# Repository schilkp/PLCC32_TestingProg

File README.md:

# PLCC_TestingProg
### Philipp Schilk

A board for programming/testing the SST39SF040 flash IC. 
It includes a PLCC32 Socket, breakouts of the Data, Address and Control Lines,
and optional shift registers to drive the address lines during programming.

Furthermore, if nothing but the PLCC32 socket is fitted, it may serve as a direct
breakout. 

Designed for the SST39SF040, but also usable with all other chips in the family
(F020, F010). Could be compatible with many other flash chips with similar layout. 

## Overview

**Doc:**
	Documentation

**Gerber:**
	Gerber Files for PCB Manufacture

**KiCad:**
    KiCad Project Files (Schematic and PCB).
    Download KiCad at [kicad-pcb.org](https://kicad-pcb.org/download/).

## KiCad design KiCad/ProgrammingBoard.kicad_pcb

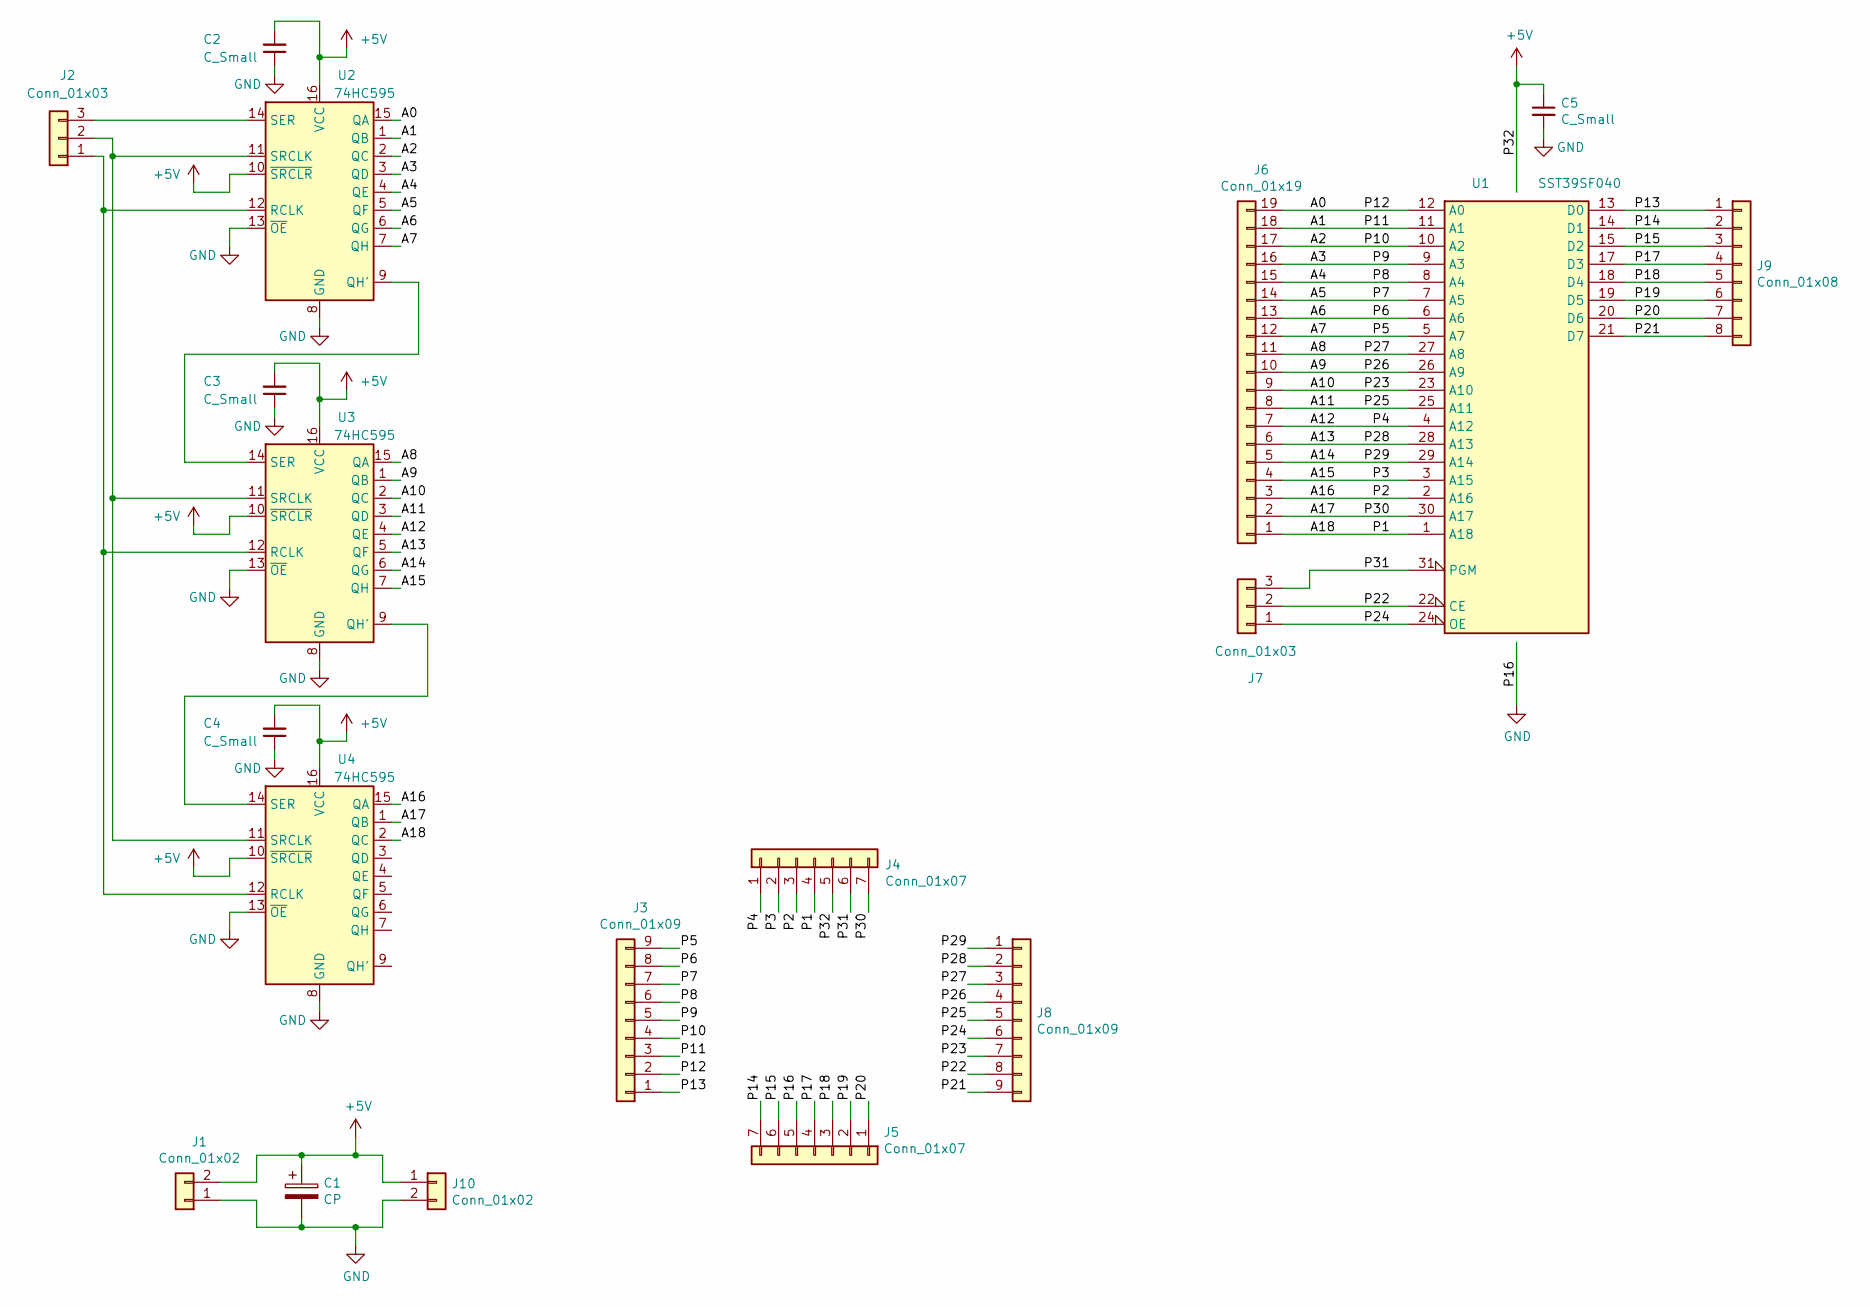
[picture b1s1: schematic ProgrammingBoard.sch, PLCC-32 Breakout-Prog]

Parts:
C1: CP; CP_Elec_8x6.5
C2, C3, C4, C5: C_Small; C_0603_1608Metric
J1, J10: Conn_01x02; PinHeader_1x02_P2.54mm_Vertical
J2, J7: Conn_01x03; PinHeader_1x03_P2.54mm_Vertical
J3, J8: Conn_01x09; PinHeader_1x09_P2.54mm_Vertical
J4, J5: Conn_01x07; PinHeader_1x07_P2.54mm_Vertical
J6: Conn_01x19; PinHeader_2x10_P2.54mm_Vertical
J9: Conn_01x08; PinHeader_1x08_P2.54mm_Vertical
U1: SST39SF040; PLCC-32_11.4x14.0mm_P1.27mm
U2, U3, U4: 74HC595; TSSOP-16_4.4x5mm_P0.65mm

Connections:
+5V: C1.1, C2.2, C3.2, C4.2, C5.1, J1.2, J4.5, J10.1, U1.32 (VCC), U2.10 (~SRCLR), U2.16 (VCC), U3.10 (~SRCLR), U3.16 (VCC), U4.10 (~SRCLR), U4.16 (VCC)
/A0: J3.2, J6.19, U1.12 (A0), U2.15 (QA)
/A1: J3.3, J6.18, U1.11 (A1), U2.1 (QB)
/A2: J3.4, J6.17, U1.10 (A2), U2.2 (QC)
/A3: J3.5, J6.16, U1.9 (A3), U2.3 (QD)
/A4: J3.6, J6.15, U1.8 (A4), U2.4 (QE)
/A5: J3.7, J6.14, U1.7 (A5), U2.5 (QF)
/A6: J3.8, J6.13, U1.6 (A6), U2.6 (QG)
/A7: J3.9, J6.12, U1.5 (A7), U2.7 (QH)
/A8: J6.11, J8.3, U1.27 (A8), U3.15 (QA)
/A9: J6.10, J8.4, U1.26 (A9), U3.1 (QB)
/A10: J6.9, J8.7, U1.23 (A10), U3.2 (QC)
/A11: J6.8, J8.5, U1.25 (A11), U3.3 (QD)
/A12: J4.1, J6.7, U1.4 (A12), U3.4 (QE)
/A13: J6.6, J8.2, U1.28 (A13), U3.5 (QF)
/A14: J6.5, J8.1, U1.29 (A14), U3.6 (QG)
/A15: J4.2, J6.4, U1.3 (A15), U3.7 (QH)
/A16: J4.3, J6.3, U1.2 (A16), U4.15 (QA)
/A17: J4.7, J6.2, U1.30 (A17), U4.1 (QB)
/A18: J4.4, J6.1, U1.1 (A18), U4.2 (QC)
/P13: J3.1, J9.1, U1.13 (D0)
/P14: J5.7, J9.2, U1.14 (D1)
/P15: J5.6, J9.3, U1.15 (D2)
/P17: J5.4, J9.4, U1.17 (D3)
/P18: J5.3, J9.5, U1.18 (D4)
/P19: J5.2, J9.6, U1.19 (D5)
/P20: J5.1, J9.7, U1.20 (D6)
/P21: J8.9, J9.8, U1.21 (D7)
/P22: J7.2, J8.8, U1.22 (CE)
/P24: J7.1, J8.6, U1.24 (OE)
/P31: J4.6, J7.3, U1.31 (PGM)
GND: C1.2, C2.1, C3.1, C4.1, C5.2, J1.1, J5.5, J10.2, U1.16 (GND), U2.8 (GND), U2.13 (~OE), U3.8 (GND), U3.13 (~OE), U4.8 (GND), U4.13 (~OE)
unnamed: J2.1, U2.12 (RCLK), U3.12 (RCLK), U4.12 (RCLK)
unnamed: J2.2, U2.11 (SRCLK), U3.11 (SRCLK), U4.11 (SRCLK)
unnamed: J2.3, U2.14 (SER)
unnamed: U2.9 (QH'), U3.14 (SER)
unnamed: U3.9 (QH'), U4.14 (SER)

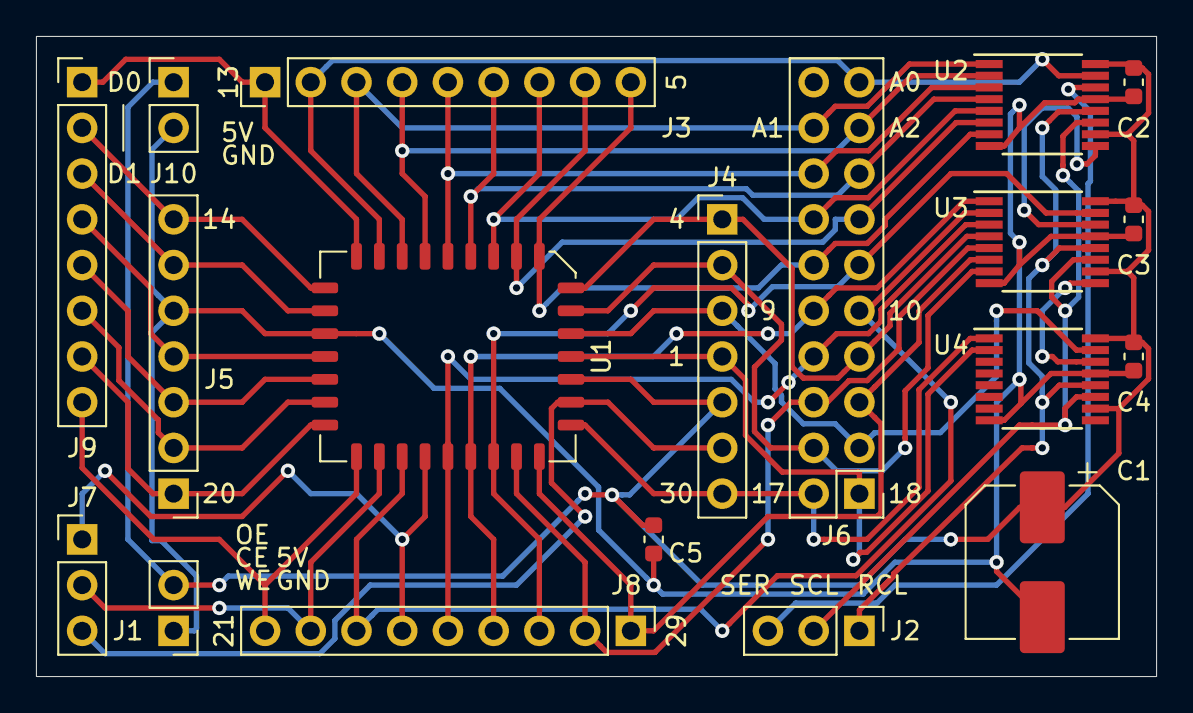
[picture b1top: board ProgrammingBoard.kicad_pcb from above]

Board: 2 copper layers, 62.2 x 35.6 mm, 19 parts (0 on the bottom side), 37 nets.

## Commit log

2020-02-13 v0.0 - Initial Commit
    State of project at production of PCB v0.0
2020-02-14 Added Render of PCB v0.0
2020-02-14 Added MIT License
2020-03-19 Moved silkscreen covered by PLCC-32 Socket
2021-05-24 Added .gitattributes
